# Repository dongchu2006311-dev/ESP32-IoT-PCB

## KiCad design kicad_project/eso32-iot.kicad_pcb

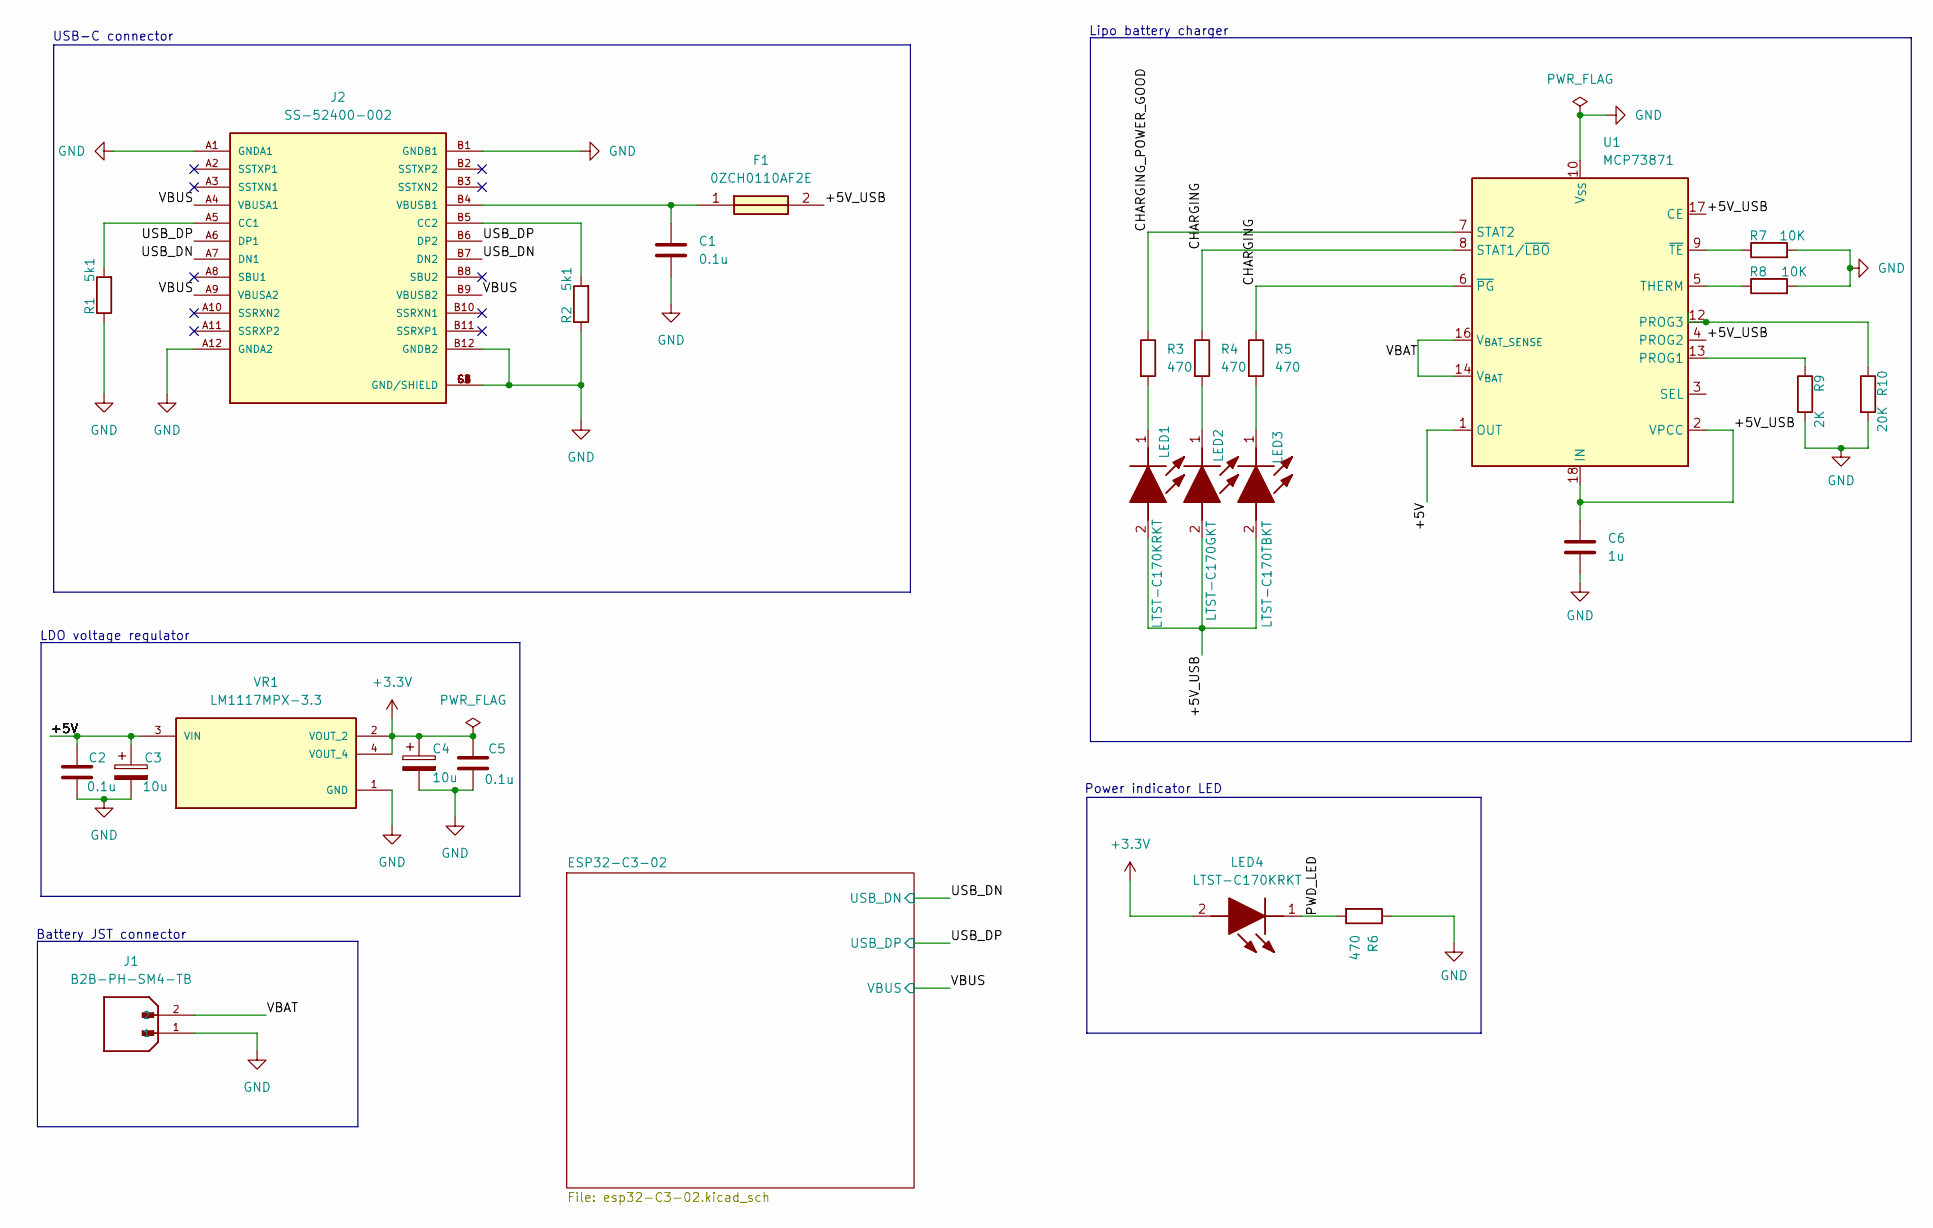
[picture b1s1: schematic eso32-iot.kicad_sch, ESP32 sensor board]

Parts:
C1, C2, C5: 0.1u; C_0805_2012Metric
C3, C4: 10u; T491A
C6: 1u; C_0805_2012Metric
F1: 0ZCH0110AF2E; FUSC3226X100N; Manufacturer_Part_Number 0ZCH0110AF2E
J1: B2B-PH-SM4-TB; JST_B2B-PH-SM4-TB; PARTREV N/A
J2: SS-52400-002; BELFUSE_SS-52400-002; PARTREV A0
LED1, LED4: LTST-C170KRKT; LEDC2012X120N; Manufacturer_Part_Number LTST-C170KRKT; Mouser Part Number 859-LTST-C170KRKT
LED2: LTST-C170GKT; LEDC2012X120N; Manufacturer_Part_Number LTST-C170GKT; Mouser Part Number 859-LTST-C170GKT
LED3: LTST-C170TBKT; LEDC2012X120N; Manufacturer_Part_Number LTST-C170TBKT; Mouser Part Number 859-LTST-C170TBKT
R1, R2: 5k1; R_0805_2012Metric
R3, R4, R5, R6: 470; R_0805_2012Metric
R7, R8: 10K; R_0805_2012Metric
R9: 2K; R_0805_2012Metric
R10: 20K; R_0805_2012Metric
U1: MCP73871; QFN-20-1EP_4x4mm_P0.5mm_EP2.5x2.5mm
VR1: LM1117MPX-3.3; VREG_LM1117MPX-3.3

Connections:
+3.3V: C4.1, C5.1, LED4.2 (A), VR1.2 (VOUT_2), VR1.4 (VOUT_4); also elsewhere on the board
/+5V: C2.1, C3.1, U1.1 (OUT), U1.20 (OUT), VR1.3 (VIN)
/+5V_USB: C6.1, F1.2, LED1.2 (A), LED2.2 (A), LED3.2 (A), U1.2 (VPCC), U1.4 (PROG2), U1.17 (CE), U1.18 (IN), U1.19 (IN)
/CHARGING_POWER_GOOD: R3.1, U1.7 (STAT2)
/PWD_LED: LED4.1 (K), R6.2
/USB_DN: J2.A7 (DN1), J2.B7 (DN2)
/USB_DP: J2.A6 (DP1), J2.B6 (DP2)
/VBUS: J2.A4 (VBUSA1), J2.A9 (VBUSA2), J2.B9 (VBUSB2); also elsewhere on the board
GND: C1.1, C2.2, C3.2, C4.2, C5.2, C6.2, J1.1, J2.A1 (GNDA1), J2.A12 (GNDA2), J2.B1 (GNDB1), J2.B12 (GNDB2), J2.G1 (GND/SHIELD), J2.G2 (GND/SHIELD), J2.G3 (GND/SHIELD), J2.G4 (GND/SHIELD), J2.S1 (GND/SHIELD), J2.S2 (GND/SHIELD), J2.S3 (GND/SHIELD), J2.S4 (GND/SHIELD), R1.1, R2.1, R6.1, R7.2, R8.2, R9.2, R10.2, U1.10 (V_{SS}), U1.11 (V_{SS}), U1.21 (V_{SS}), VR1.1 (GND); also elsewhere on the board
unnamed: J2.A5 (CC1), R1.2
unnamed: J2.B5 (CC2), R2.2
unnamed: C1.2, F1.1, J2.B4 (VBUSB1)
unnamed: LED1.1 (K), R3.2
unnamed: LED2.1 (K), R4.2
unnamed: LED3.1 (K), R5.2
unnamed: R9.1, U1.13 (PROG1)
unnamed: R10.1, U1.12 (PROG3)
unnamed: R8.1, U1.5 (THERM)
unnamed: R7.1, U1.9 (~TE)

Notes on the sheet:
USB-C connector
LDO voltage regulator
Power indicator LED
Lipo battery charger
Battery JST connector

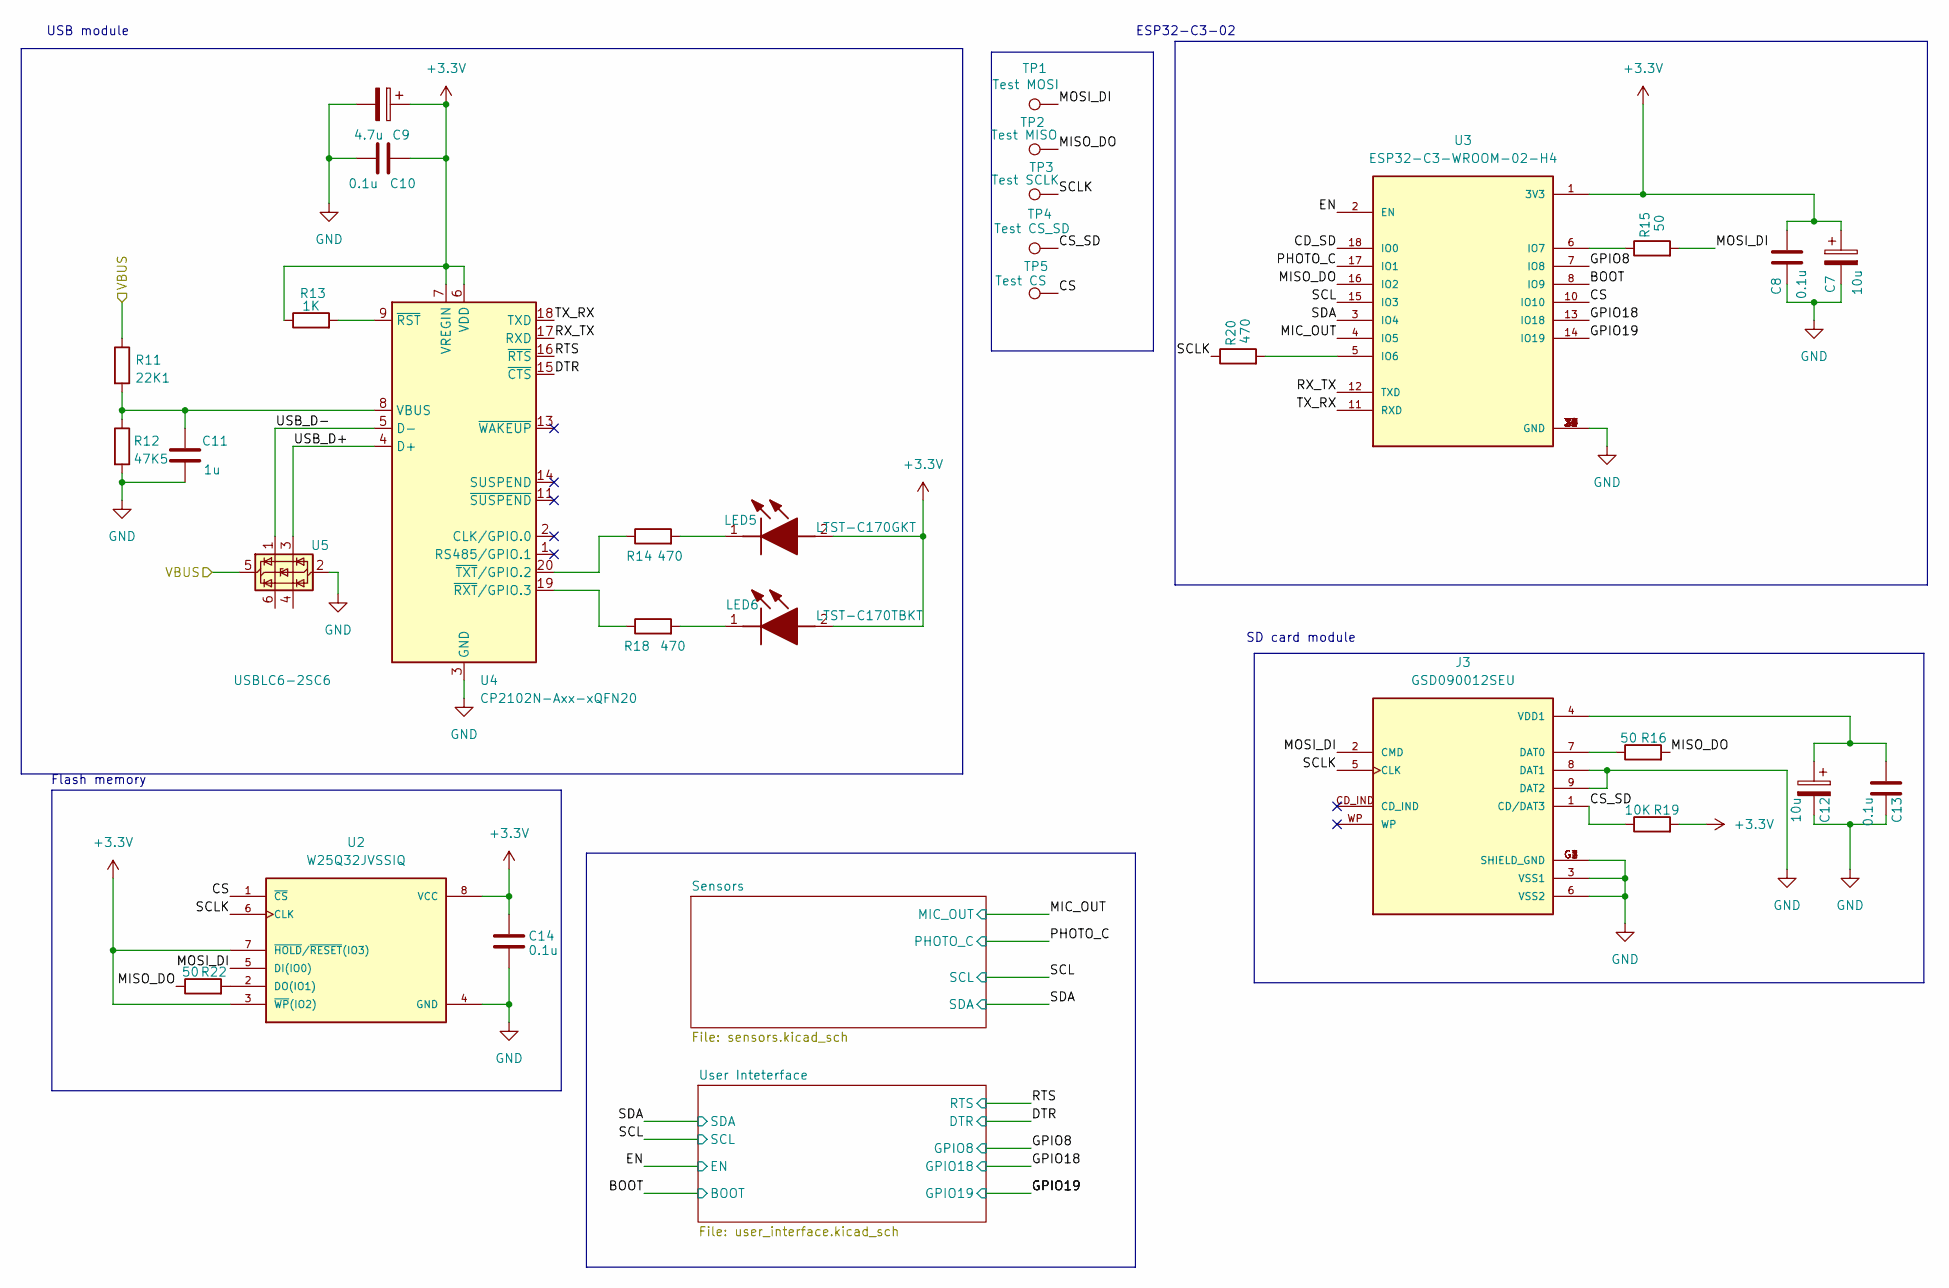
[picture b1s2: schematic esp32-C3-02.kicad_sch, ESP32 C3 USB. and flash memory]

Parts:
C7, C12: 10u; T491A
C8, C10, C13, C14: 0.1u; C_0805_2012Metric
C9: 4.7u; T491A
C11: 1u; C_0805_2012Metric
J3: GSD090012SEU; AMPHENOL_GSD090012SEU; PARTREV E
LED5: LTST-C170GKT; LEDC2012X120N; Manufacturer_Part_Number LTST-C170GKT; Mouser Part Number 859-LTST-C170GKT
LED6: LTST-C170TBKT; LEDC2012X120N; Manufacturer_Part_Number LTST-C170TBKT; Mouser Part Number 859-LTST-C170TBKT
R11: 22K1; R_0805_2012Metric
R12: 47K5; R_0805_2012Metric
R13: 1K; R_0805_2012Metric
R14, R18, R20: 470; R_0805_2012Metric
R15, R16, R22: 50; R_0805_2012Metric
R19: 10K; R_0805_2012Metric
TP1: Test MOSI; TestPoint_Pad_D1.0mm
TP2: Test MISO; TestPoint_Pad_D1.0mm
TP3: Test SCLK; TestPoint_Pad_D1.0mm
TP4: Test CS_SD; TestPoint_Pad_D1.0mm
TP5: Test CS; TestPoint_Pad_D1.0mm
U2: W25Q32JVSSIQ; SOIC127P790X216-8N; M_PART_NUMBER W25QXX
U3: ESP32-C3-WROOM-02-H4; MODULE_ESP32-C3-WROOM-02-H4
U4: CP2102N-Axx-xQFN20; QFN50P400X400X100-21N
U5: USBLC6-2SC6; SOT-23-6

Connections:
+3.3V: C7.1, C8.1, C9.1, C10.2, C14.1, LED5.2 (A), LED6.2 (A), R13.1, R19.2, U2.3 (~WP(IO2)), U2.7 (~HOLD/~RESET(IO3)), U2.8 (VCC), U3.1 (3V3), U4.6 (VDD), U4.7 (VREGIN); also elsewhere on the board
/ESP32-C3-02/BOOT: U3.8 (IO9); also elsewhere on the board
/ESP32-C3-02/CD_SD: U3.18 (IO0)
/ESP32-C3-02/CS: TP5.1 (1_1), U2.1 (~CS), U3.10 (IO10)
/ESP32-C3-02/CS_SD: J3.1 (CD/DAT3), R19.1, TP4.1 (1_1)
/ESP32-C3-02/DTR: U4.15 (~CTS); also elsewhere on the board
/ESP32-C3-02/EN: U3.2 (EN); also elsewhere on the board
/ESP32-C3-02/GPIO8: U3.7 (IO8); also elsewhere on the board
/ESP32-C3-02/GPIO18: U3.13 (IO18); also elsewhere on the board
/ESP32-C3-02/GPIO19: U3.14 (IO19); also elsewhere on the board
/ESP32-C3-02/MIC_OUT: U3.4 (IO5); also elsewhere on the board
/ESP32-C3-02/MISO_DO: R16.2, R22.1, TP2.1 (1_1), U3.16 (IO2)
/ESP32-C3-02/MOSI_DI: J3.2 (CMD), R15.2, TP1.1 (1_1), U2.5 (DI(IO0))
/ESP32-C3-02/PHOTO_C: U3.17 (IO1); also elsewhere on the board
/ESP32-C3-02/RTX: U4.16 (~RTS); also elsewhere on the board
/ESP32-C3-02/RX_TX: U3.12 (TXD), U4.17 (RXD)
/ESP32-C3-02/SCL: U3.15 (IO3); also elsewhere on the board
/ESP32-C3-02/SCLK: J3.5 (CLK), R20.1, TP3.1 (1_1), U2.6 (CLK)
/ESP32-C3-02/SDA: U3.3 (IO4); also elsewhere on the board
/ESP32-C3-02/TX_RX: U3.11 (RXD), U4.18 (TXD)
/ESP32-C3-02/USB_D+: U4.4 (D+), U5.3 (I/O2)
/ESP32-C3-02/USB_D-: U4.5 (D-), U5.1 (I/O1)
/VBUS: R11.1, U5.5 (VBUS); also elsewhere on the board
GND: C7.2, C8.2, C9.2, C10.1, C11.2, C12.2, C13.2, C14.2, J3.3 (VSS1), J3.6 (VSS2), J3.8 (DAT1), J3.9 (DAT2), J3.G1 (SHIELD_GND), J3.G2 (SHIELD_GND), J3.G3 (SHIELD_GND), J3.G4 (SHIELD_GND), R12.2, U2.4 (GND), U3.9 (GND), U3.19 (GND), U3.20 (GND), U3.21 (GND), U3.22 (GND), U3.23 (GND), U3.24 (GND), U3.25 (GND), U3.26 (GND), U3.27 (GND), U3.28 (GND), U3.29 (GND), U3.30 (GND), U3.31 (GND), U3.32 (GND), U3.33 (GND), U3.34 (GND), U3.35 (GND), U3.36 (GND), U3.37 (GND), U3.38 (GND), U3.39 (GND), U4.3 (GND), U4.12 (GND), U4.21 (GND), U5.2 (GND); also elsewhere on the board
unnamed: J3.7 (DAT0), R16.1
unnamed: C12.1, C13.1, J3.4 (VDD1)
unnamed: LED5.1 (K), R14.2
unnamed: LED6.1 (K), R18.2
unnamed: R22.2, U2.2 (DO(IO1))
unnamed: R20.2, U3.5 (IO6)
unnamed: R15.1, U3.6 (IO7)
unnamed: C11.1, R11.2, R12.1, U4.8 (VBUS)
unnamed: R13.2, U4.9 (~RST)
unnamed: R18.1, U4.19 (~RXT/GPIO.3)
unnamed: R14.1, U4.20 (~TXT/GPIO.2)

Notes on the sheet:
Flash memory
SD card module
ESP32-C3-02
USB module

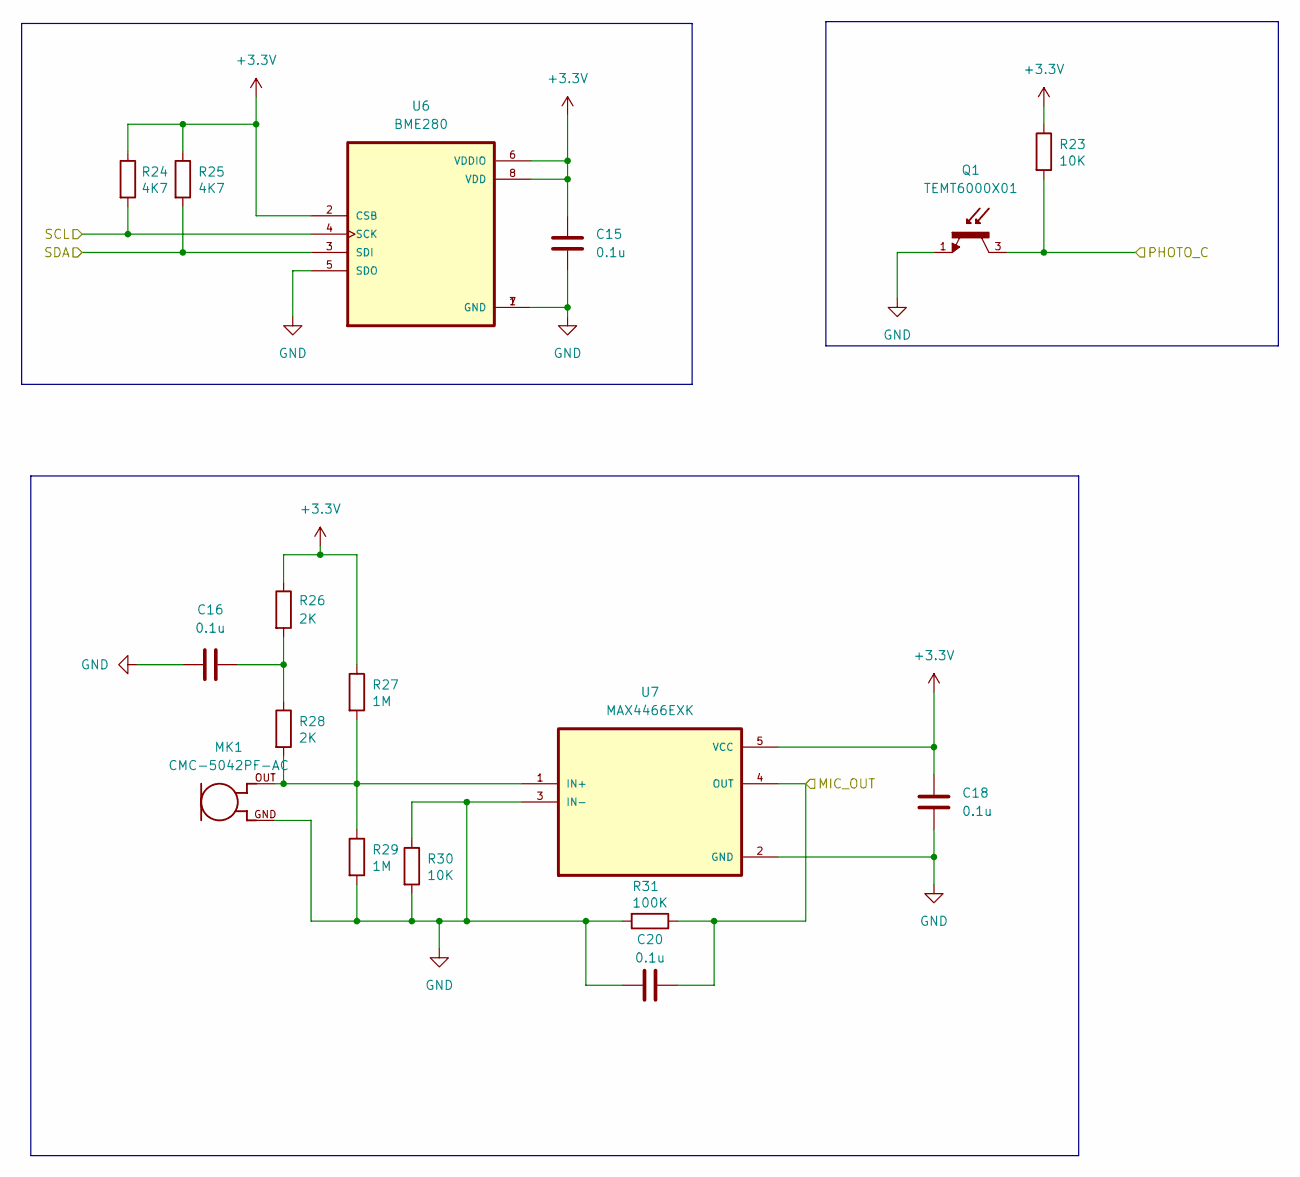
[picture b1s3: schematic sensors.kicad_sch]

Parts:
C15, C16, C18, C20: 0.1u; C_0805_2012Metric
MK1: CMC-5042PF-AC; CUI_CMC-5042PF-AC
Q1: TEMT6000X01; TRANS_TEMT6000X01; PARTREV 1.9
R23, R30: 10K; R_0805_2012Metric
R24, R25: 4K7; R_0805_2012Metric
R26, R28: 2K; R_0805_2012Metric
R27, R29: 1M; R_0805_2012Metric
R31: 100K; R_0805_2012Metric
U6: BME280; PSON65P250X250X100-8N
U7: MAX4466EXK; SOT65P210X110-5N

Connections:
+3.3V: C15.1, C18.1, R23.1, R24.1, R25.1, R26.1, R27.1, U6.2 (CSB), U6.6 (VDDIO), U6.8 (VDD), U7.5 (VCC); also elsewhere on the board
/ESP32-C3-02/MIC_OUT: C20.2, R31.1, U7.4 (OUT); also elsewhere on the board
/ESP32-C3-02/PHOTO_C: Q1.3, R23.2; also elsewhere on the board
/ESP32-C3-02/SCL: R24.2, U6.4 (SCK); also elsewhere on the board
/ESP32-C3-02/SDA: R25.2, U6.3 (SDI); also elsewhere on the board
GND: C15.2, C16.2, C18.2, C20.1, MK1.GND, Q1.1, R29.2, R30.1, R30.2, R31.2, U6.1 (GND), U6.5 (SDO), U6.7 (GND), U7.2 (GND), U7.3 (IN-); also elsewhere on the board
unnamed: C16.1, R26.2, R28.1
unnamed: MK1.OUT, R27.2, R28.2, R29.1, U7.1 (IN+)

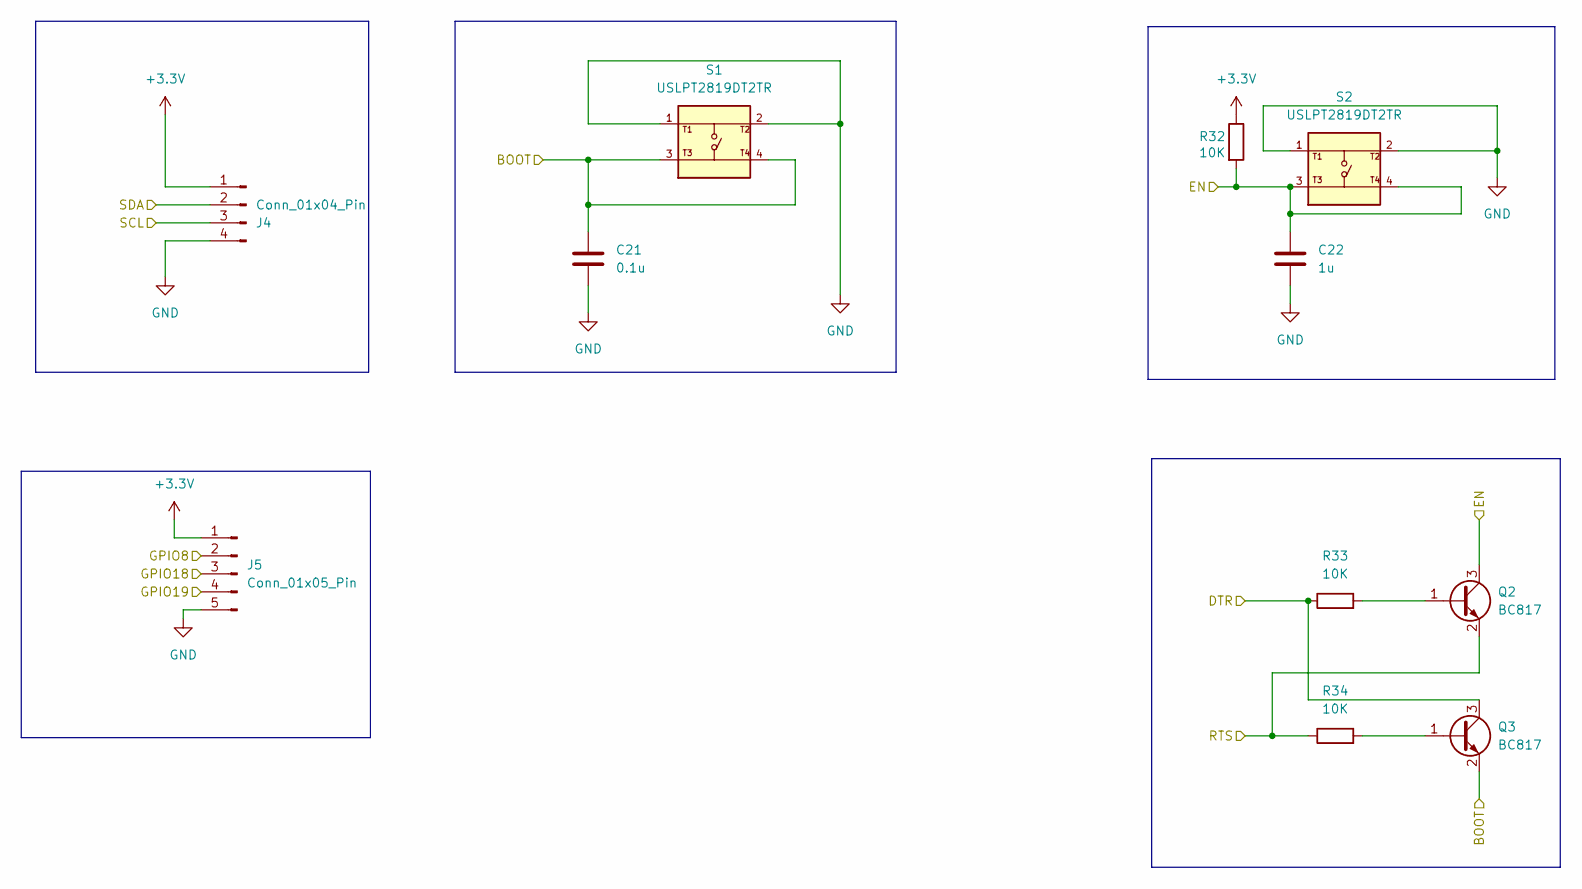
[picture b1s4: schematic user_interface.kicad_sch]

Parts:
C21: 0.1u; C_0805_2012Metric
C22: 1u; C_0805_2012Metric
J4: Conn_01x04_Pin; PinHeader_1x04_P2.54mm_Vertical
J5: Conn_01x05_Pin; PinHeader_1x05_P2.54mm_Vertical
Q2, Q3: BC817; SOT-23
R32, R33, R34: 10K; R_0805_2012Metric
S1, S2: USLPT2819DT2TR; SW_USLPT2819DT2TR; PARTREV P

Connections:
+3.3V: J4.1, J5.1, R32.1; also elsewhere on the board
/ESP32-C3-02/BOOT: C21.1, Q3.2 (E), S1.3, S1.4; also elsewhere on the board
/ESP32-C3-02/DTR: Q3.3 (C), R33.1; also elsewhere on the board
/ESP32-C3-02/EN: C22.1, Q2.3 (C), R32.2, S2.3, S2.4; also elsewhere on the board
/ESP32-C3-02/GPIO8: J5.2; also elsewhere on the board
/ESP32-C3-02/GPIO18: J5.3; also elsewhere on the board
/ESP32-C3-02/GPIO19: J5.4; also elsewhere on the board
/ESP32-C3-02/RTX: Q2.2 (E), R34.1; also elsewhere on the board
/ESP32-C3-02/SCL: J4.3; also elsewhere on the board
/ESP32-C3-02/SDA: J4.2; also elsewhere on the board
GND: C21.2, C22.2, J4.4, J5.5, S1.1, S1.2, S2.1, S2.2; also elsewhere on the board
unnamed: Q2.1 (B), R33.2
unnamed: Q3.1 (B), R34.2

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
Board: 4 copper layers, 83 parts (0 on the bottom side), 56 nets, no tracks yet.
